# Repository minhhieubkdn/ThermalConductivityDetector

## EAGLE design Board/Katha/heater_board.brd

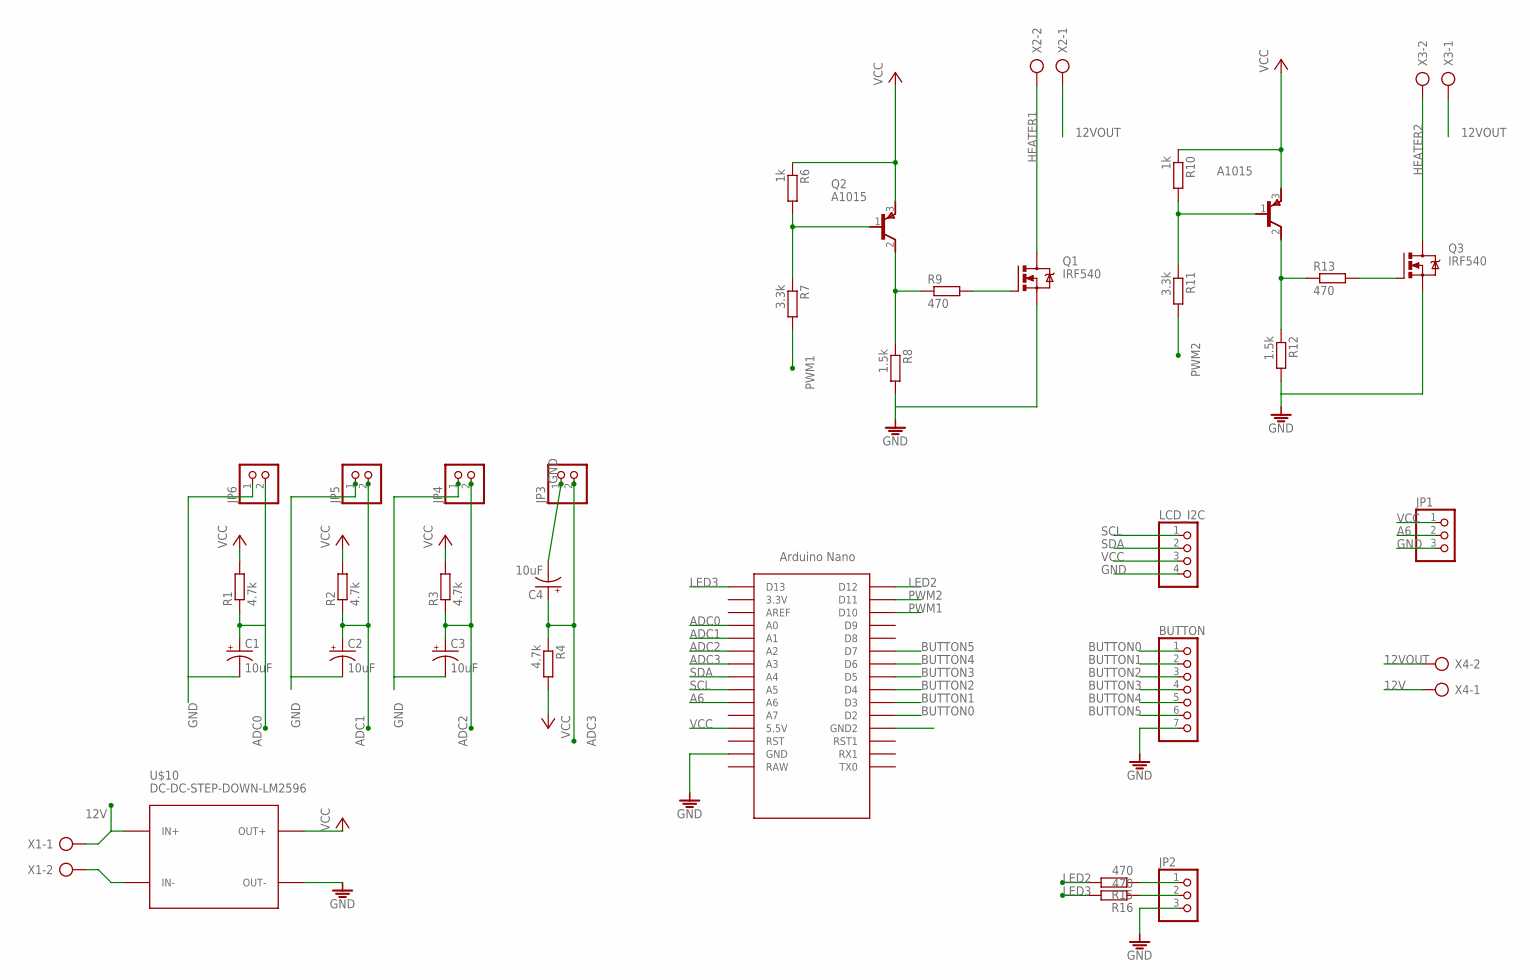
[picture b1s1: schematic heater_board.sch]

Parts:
A1015: A1015; TO92L
BUTTON: PINHD-1X7; 1X07
C1, C2, C3, C4: 10uF; E2,5-5
JP1, JP2: PINHD-1X3; 1X03
JP3, JP4, JP5, JP6: PINHD-1X2; 1X02
LCD_I2C: PINHD-1X4; 1X04
Q1, Q3: IRF540; TO220BV
Q2: A1015; TO92L
R1, R2, R3, R4: 4.7k; 0207/10
R6, R10: 1k; 0207/10
R7, R11: 3.3k; 0207/10
R8, R12: 1.5k; 0207/10
R9, R13, R15, R16: 470; 0207/10
U$1: NANO
U$10: DC-DC-STEP-DOWN-LM2596
X1, X2, X3, X4: AK300/2

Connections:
12V: U$10.IN+, X1.1, X4.1
12VOUT: X2.1, X3.1, X4.2
A6: JP1.2, U$1.A6
ADC0: C1.+, JP6.2, R1.1, U$1.A0
ADC1: C2.+, JP5.2, R2.1, U$1.A1
ADC2: C3.+, JP4.2, R3.1, U$1.A2
ADC3: C4.+, JP3.2, R4.1, U$1.A3
BUTTON0: BUTTON.1, U$1.D2
BUTTON1: BUTTON.2, U$1.D3
BUTTON2: BUTTON.3, U$1.D4
BUTTON3: BUTTON.4, U$1.D5
BUTTON4: BUTTON.5, U$1.D6
BUTTON5: BUTTON.6, U$1.D7
GND: BUTTON.7, C1.-, C2.-, C3.-, C4.-, JP1.3, JP2.3, JP3.1, JP4.1, JP5.1, JP6.1, LCD_I2C.4, Q1.S, Q3.S, R8.2, R12.2, U$1.GND, U$1.GND1 (GND2), U$10.IN-, U$10.OUT-, X1.2
HEATER1: Q1.D, X2.2
HEATER2: Q3.D, X3.2
LED2: R15.2, U$1.D12
LED3: R16.2, U$1.D13
unnamed: Q1.G, R9.2
unnamed: JP2.1, R15.1
unnamed: JP2.2, R16.1
unnamed: Q2.2 (C), R8.1, R9.1
unnamed: Q3.G, R13.2
unnamed: Q2.1 (B), R6.2, R7.1
unnamed: A1015.2 (C), R12.1, R13.1
unnamed: A1015.1 (B), R10.2, R11.1
PWM1: R7.2, U$1.D10
PWM2: R11.2, U$1.D11
SCL: LCD_I2C.1, U$1.A5
SDA: LCD_I2C.2, U$1.A4
VCC: A1015.3 (E), JP1.1, LCD_I2C.3, Q2.3 (E), R1.2, R2.2, R3.2, R4.2, R6.1, R10.1, U$1.5V (5.5V), U$10.OUT+

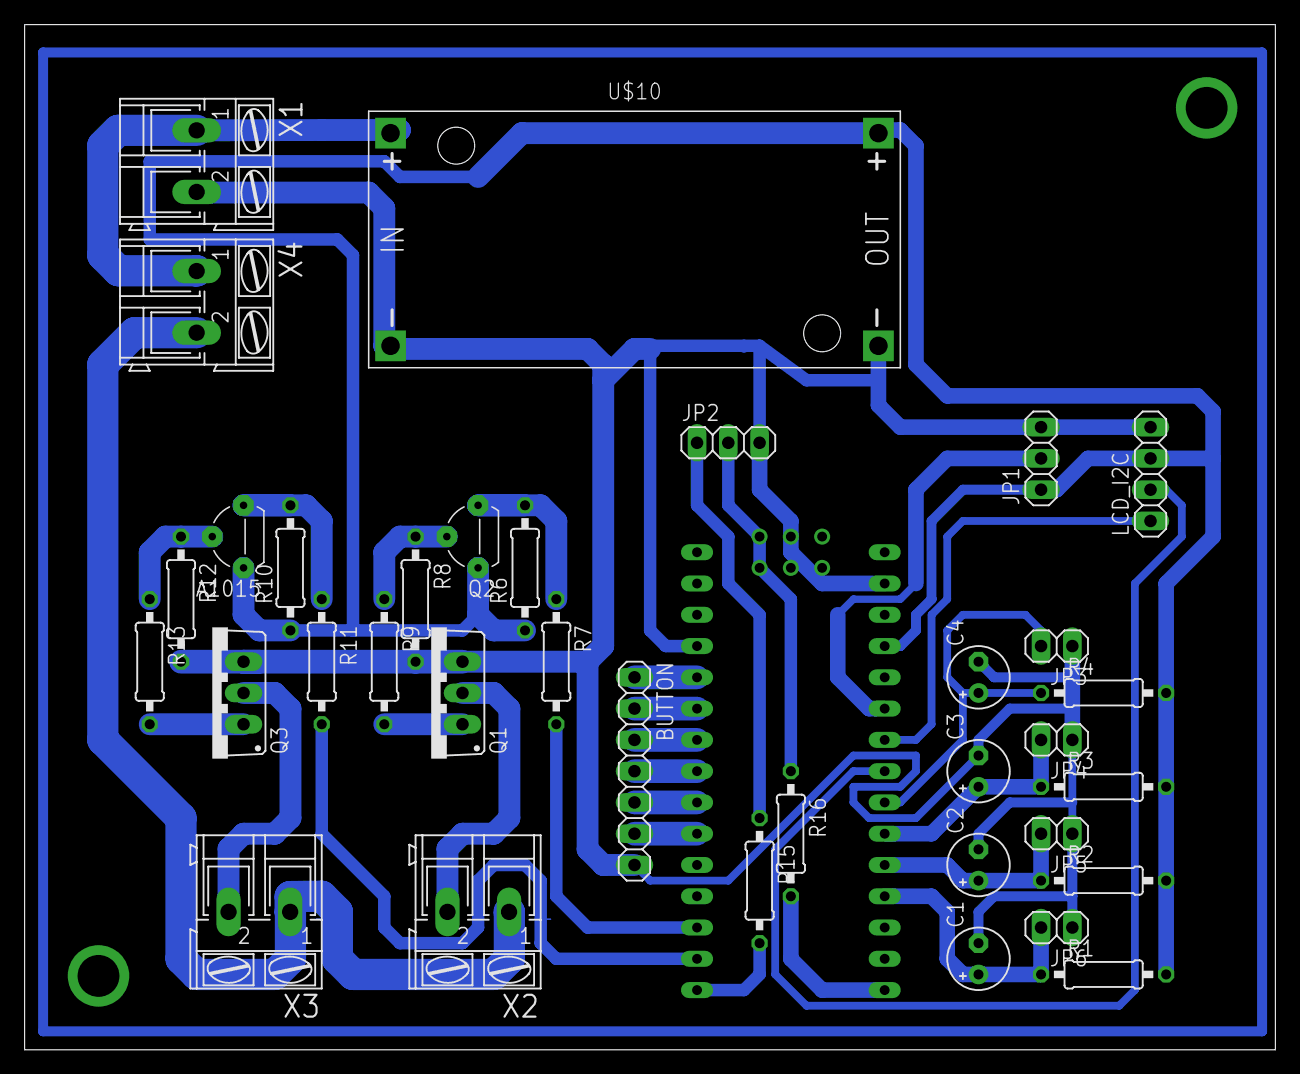
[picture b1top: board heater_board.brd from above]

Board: 2 copper layers, 101.6 x 83.3 mm, 36 parts (0 on the bottom side), 31 nets.

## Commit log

2019-03-30 no message
2019-03-30 board
2019-03-30 HotEnd_v1
2019-03-31 31/3 commit add Thermistor class sample code in .ino files
2019-04-05 bug lcd not display menu, have no reason
2019-04-06 Last day commit(06/04/19): Code: fixed LCD Menu not display bug, haven't display temp value when the value changed yet.
2019-04-09 code: custom PID solid: tao khung moi cho may
2019-04-22 stable 1.1
2019-04-25 test v1 commit

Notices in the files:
parts and their libraries:
diy-modules: Released under the Creative Commons Attribution 4.0 International License: http://creativecommons.org/licenses/by/4.0
